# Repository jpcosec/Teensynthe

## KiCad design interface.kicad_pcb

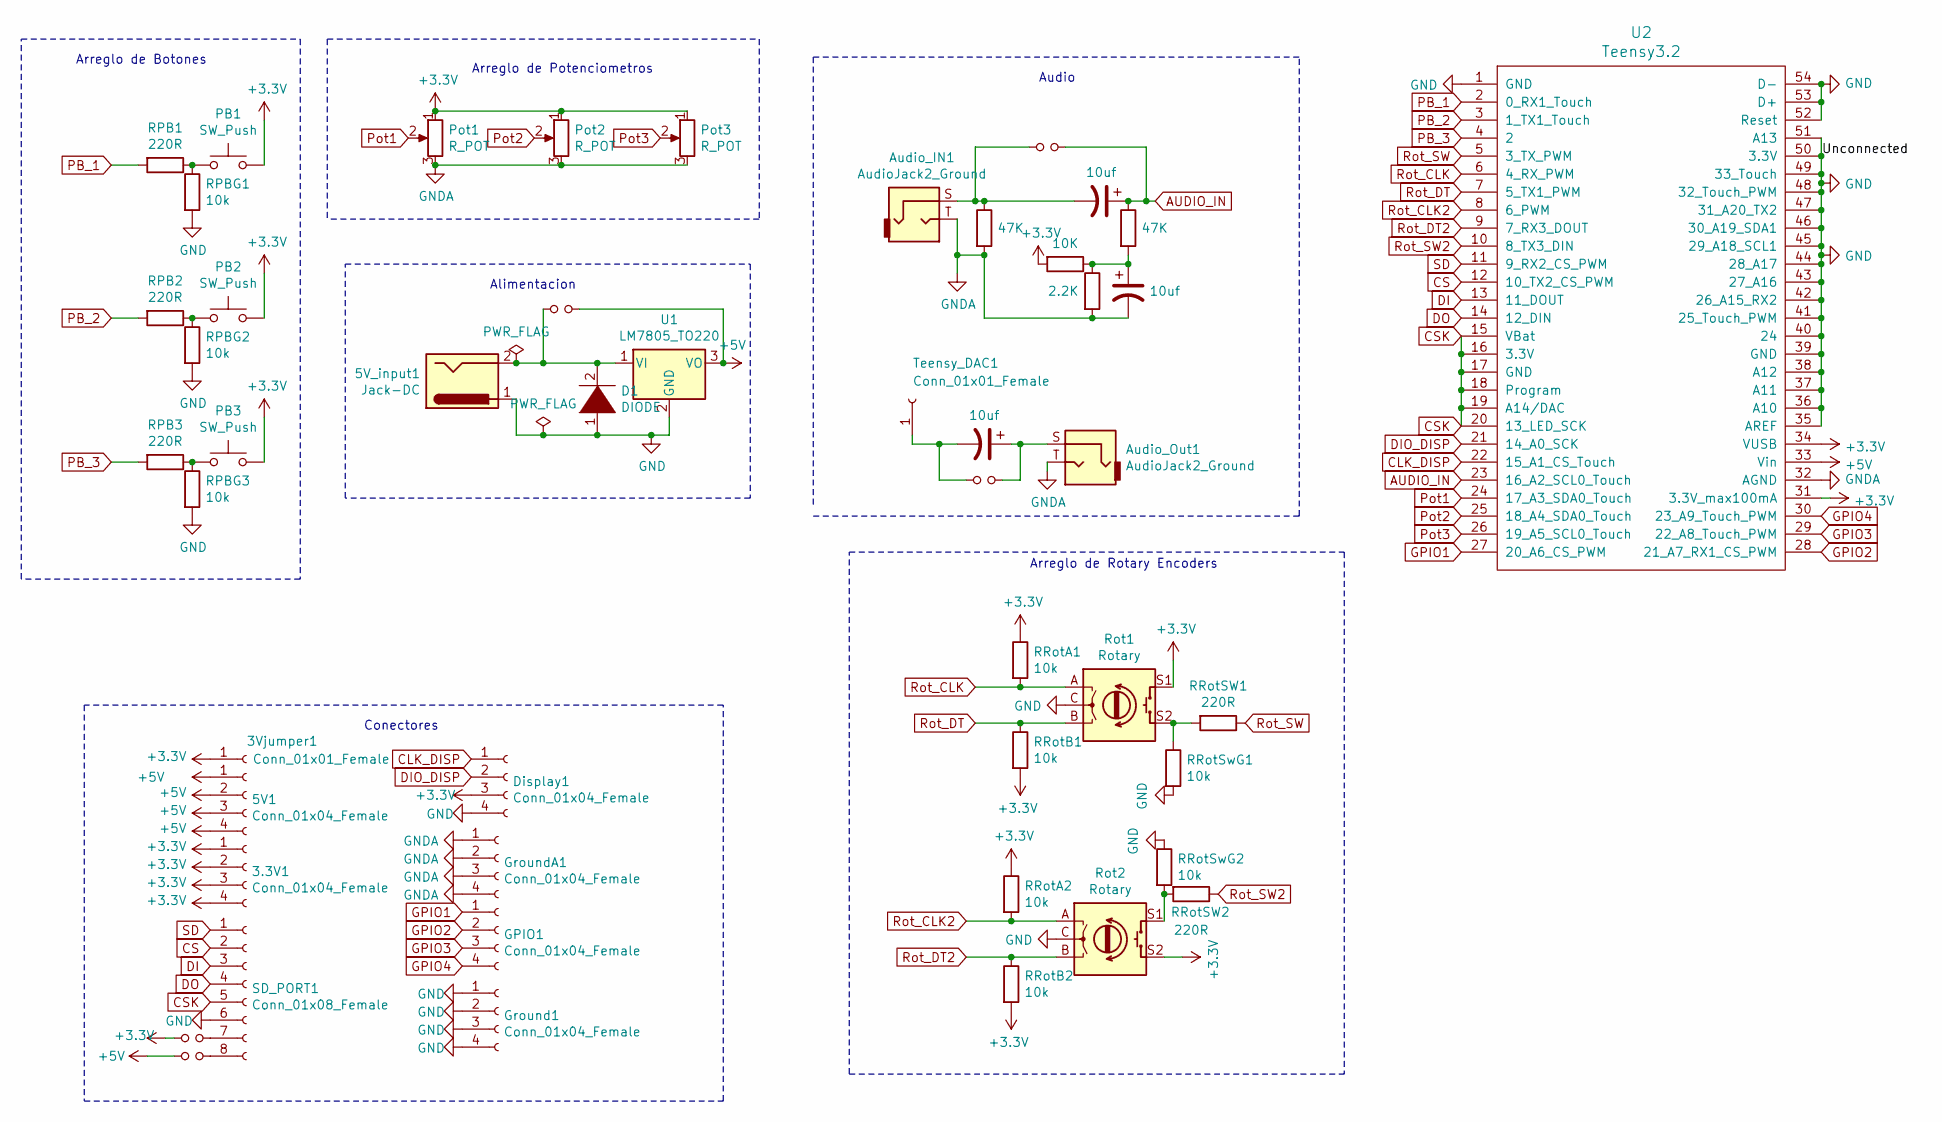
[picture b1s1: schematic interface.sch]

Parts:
3.3V1, 5V1: Conn_01x04_Female; Pin_Header_Straight_1x04_Pitch2.54mm
3Vjumper1: Conn_01x01_Female; Socket_Strip_Angled_1x01_Pitch2.00mm
5V_input1: Jack-DC; BarrelJack_Horizontal
Audio_IN1: AudioJack2_Ground; Jack_3.5mm_QingPu_WQP-PJ398SM_Vertical_CircularHoles
Audio_InC1, Audio_InC3: 10uf; CP_Radial_D8.0mm_P2.50mm
Audio_InR1, Audio_InR4: 47K; R_Axial_DIN0411_L9.9mm_D3.6mm_P12.70mm_Horizontal
Audio_InR2: 10K; R_Axial_DIN0411_L9.9mm_D3.6mm_P12.70mm_Horizontal
Audio_InR3: 2.2K; R_Axial_DIN0411_L9.9mm_D3.6mm_P12.70mm_Horizontal
Audio_Out1: AudioJack2_Ground; Jack_3.5mm_QingPu_WQP-PJ398SM_Vertical_CircularHoles
Audio_OutC1: 10uf; CP_Radial_D8.0mm_P2.50mm
D1: DIODE; D_DO-27_P12.70mm_Horizontal
Display1: Conn_01x04_Female; Pin_Header_Straight_1x04_Pitch2.54mm
GPIO1: Conn_01x04_Female; Pin_Header_Straight_1x04_Pitch2.54mm
Ground1: Conn_01x04_Female; Pin_Header_Straight_1x04_Pitch2.54mm
GroundA1: Conn_01x04_Female; Pin_Header_Straight_1x04_Pitch2.54mm
JP1, JP2, JP3, JP4, JP5: Jumper_NO_Small; SolderJumper-2_P1.3mm_Open_TrianglePad1.0x1.5mm
PB1, PB2, PB3: SW_Push; SW_PUSH_6mm_h4.3mm
Pot1, Pot2, Pot3: R_POT; Potentiometer_WirePads_largePads
RPB1, RPB2, RPB3: 220R; R_Axial_DIN0411_L9.9mm_D3.6mm_P12.70mm_Horizontal
RPBG1, RPBG2, RPBG3: 10k; R_Axial_DIN0411_L9.9mm_D3.6mm_P12.70mm_Horizontal
RRotA1, RRotA2: 10k; R_Axial_DIN0411_L9.9mm_D3.6mm_P12.70mm_Horizontal
RRotB1, RRotB2: 10k; R_Axial_DIN0411_L9.9mm_D3.6mm_P12.70mm_Horizontal
RRotSW1, RRotSW2: 220R; R_Axial_DIN0411_L9.9mm_D3.6mm_P12.70mm_Horizontal
RRotSwG1, RRotSwG2: 10k; R_Axial_DIN0411_L9.9mm_D3.6mm_P12.70mm_Horizontal
Rot1, Rot2: Rotary; RotaryEncoder_Alps_EC11E-Switch_Vertical_H20mm
SD_PORT1: Conn_01x08_Female; Pin_Header_Straight_1x08_Pitch2.54mm
Teensy_DAC1: Conn_01x01_Female; Socket_Strip_Angled_1x01_Pitch2.00mm
U1: LM7805_TO220; TO-220
U2: Teensy3.2; Teensy30_31_32_LC

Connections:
+3V3: 3.3V1.1, 3.3V1.2, 3.3V1.3, 3.3V1.4, 3Vjumper1.1, Audio_InR2.2, Display1.3, JP1.1, PB1.2, PB2.2, PB3.2, Pot1.1, Pot2.1, Pot3.1, RRotA1.1, RRotA2.1, RRotB1.2, RRotB2.2, Rot1.S1, Rot2.S2, U2.31 (3.3V_max100mA), U2.34 (VUSB)
+5V: 5V1.1, 5V1.2, 5V1.3, 5V1.4, JP2.1, JP3.2, U1.3 (VO), U2.33 (Vin)
AUDIO_IN: Audio_InC1.1, Audio_InR4.1, JP5.2, U2.23 (16_A2_SCL0_Touch)
CLK_DISP: Display1.1, U2.22 (15_A1_CS_Touch)
CS: SD_PORT1.2, U2.12 (10_TX2_CS_PWM)
CSK: SD_PORT1.5, U2.15 (VBat), U2.16 (3.3V), U2.17 (GND), U2.18 (Program), U2.19 (A14/DAC), U2.20 (13_LED_SCK)
DI: SD_PORT1.3, U2.13 (11_DOUT)
DIO_DISP: Display1.2, U2.21 (14_A0_SCK)
DO: SD_PORT1.4, U2.14 (12_DIN)
GND: 5V_input1.1, D1.1 (K), Display1.4, Ground1.1, Ground1.2, Ground1.3, Ground1.4, RPBG1.2, RPBG2.2, RPBG3.2, RRotSwG1.2, RRotSwG2.1, Rot1.C, Rot2.C, SD_PORT1.6, U1.2 (GND), U2.1 (GND), U2.35 (AREF), U2.36 (A10), U2.37 (A11), U2.38 (A12), U2.39 (GND), U2.40 (24), U2.41 (25_Touch_PWM), U2.42 (26_A15_RX2), U2.43 (27_A16), U2.44 (28_A17), U2.45 (29_A18_SCL1), U2.46 (30_A19_SDA1), U2.47 (31_A20_TX2), U2.48 (32_Touch_PWM), U2.49 (33_Touch), U2.50 (3.3V), U2.51 (A13), U2.52 (Reset), U2.53 (D+), U2.54 (D-)
GNDA: Audio_IN1.T, Audio_InC3.2, Audio_InR1.2, Audio_InR3.2, Audio_Out1.T, GroundA1.1, GroundA1.2, GroundA1.3, GroundA1.4, Pot1.3, Pot2.3, Pot3.3, U2.32 (AGND)
GPIO1: GPIO1.1, U2.27 (20_A6_CS_PWM)
GPIO2: GPIO1.2, U2.28 (21_A7_RX1_CS_PWM)
GPIO3: GPIO1.3, U2.29 (22_A8_Touch_PWM)
GPIO4: GPIO1.4, U2.30 (23_A9_Touch_PWM)
unnamed: 5V_input1.2, D1.2 (A), JP3.1, U1.1 (VI)
unnamed: Audio_IN1.S, Audio_InC1.2, Audio_InR1.1, JP5.1
unnamed: Audio_InC3.1, Audio_InR2.1, Audio_InR3.1, Audio_InR4.2
unnamed: Audio_Out1.S, Audio_OutC1.1, JP4.2
unnamed: Audio_OutC1.2, JP4.1, Teensy_DAC1.1
unnamed: JP1.2, SD_PORT1.7
unnamed: JP2.2, SD_PORT1.8
unnamed: PB1.1, RPB1.1, RPBG1.1
unnamed: PB2.1, RPB2.1, RPBG2.1
unnamed: PB3.1, RPB3.1, RPBG3.1
unnamed: RRotSW1.2, RRotSwG1.1, Rot1.S2
unnamed: RRotSW2.2, RRotSwG2.2, Rot2.S1
PB_1: RPB1.2, U2.2 (0_RX1_Touch)
PB_2: RPB2.2, U2.3 (1_TX1_Touch)
PB_3: RPB3.2, U2.4 (2)
Pot1: Pot1.2, U2.24 (17_A3_SDA0_Touch)
Pot2: Pot2.2, U2.25 (18_A4_SDA0_Touch)
Pot3: Pot3.2, U2.26 (19_A5_SCL0_Touch)
Rot_CLK: RRotA1.2, Rot1.A, U2.6 (4_RX_PWM)
Rot_CLK2: RRotA2.2, Rot2.A, U2.8 (6_PWM)
Rot_DT: RRotB1.1, Rot1.B, U2.7 (5_TX1_PWM)
Rot_DT2: RRotB2.1, Rot2.B, U2.9 (7_RX3_DOUT)
Rot_SW: RRotSW1.1, U2.5 (3_TX_PWM)
Rot_SW2: RRotSW2.1, U2.10 (8_TX3_DIN)
SD: SD_PORT1.1, U2.11 (9_RX2_CS_PWM)

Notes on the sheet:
Arreglo de Potenciometros
Arreglo de Botones
Arreglo de Rotary Encoders
Alimentacion
Audio
Conectores

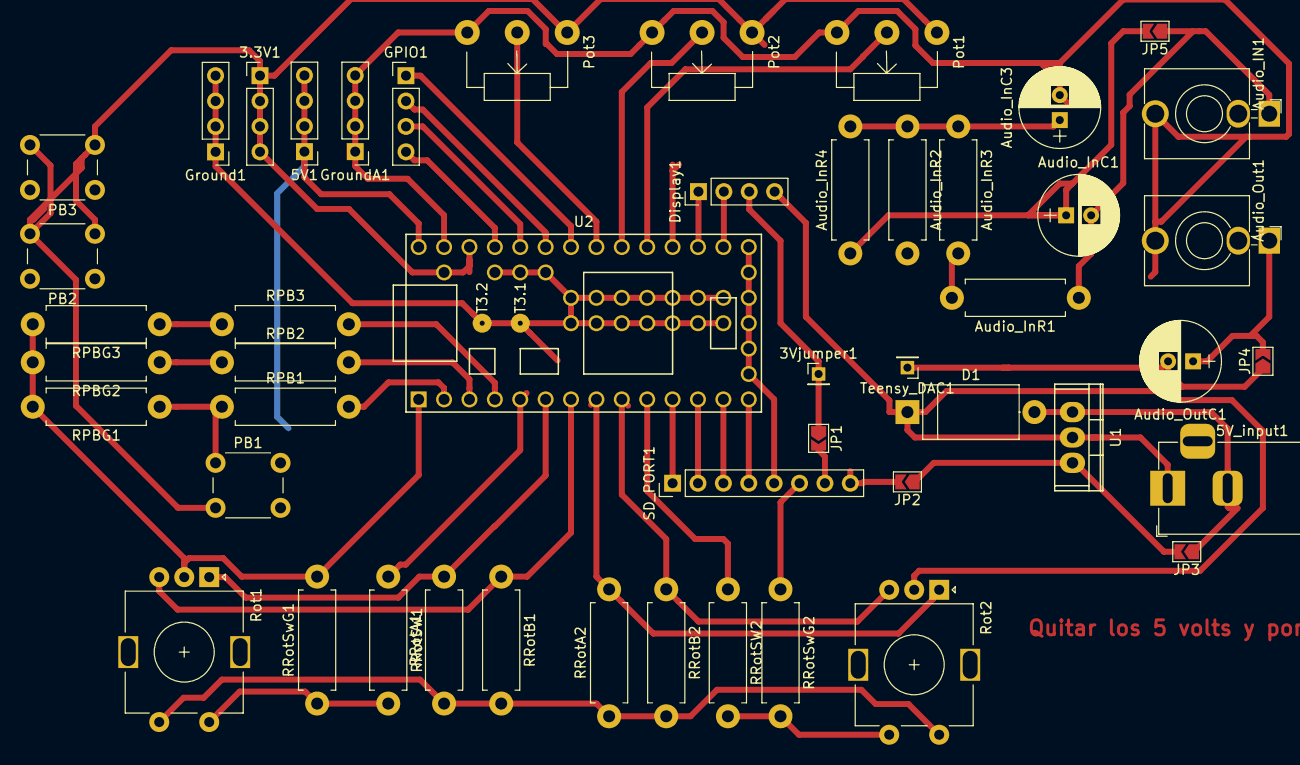
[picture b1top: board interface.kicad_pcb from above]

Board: 2 copper layers, 49 parts (0 on the bottom side), 40 nets.

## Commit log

2018-12-19 Init
    Falta terminar detalles.
    * Quitar 5 volts de SD o reemplazar por jumpers
    * Revisar el resto
